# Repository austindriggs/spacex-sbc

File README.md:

# SpaceX SBC PCB Design by Austin Driggs

## INTRODUCTION

This repository contains the complete PCB architecture and design process for a custom Single Board Computer (SBC), prepared for a technical interview presentation for a PCB Design Engineer at SpaceX before I graduated from WVU. It walks through component package selection, power budget calculations, SoC and DDR3 memory constraint analysis, and 8-layer stackup optimization.

> **Disclaimer:** This project is an independent personal design exercise created solely for educational and portfolio demonstration purposes. It is not affiliated with, endorsed by, sponsored by, or associated with Space Exploration Technologies Corp. (SpaceX). All trademarks, logos, and brand names mentioned herein belong to their respective owners.

## PRESENTATION

### Prompt

- You are working with a design engineer on a small computer board.
- The computer board has a SoC, DDR3 DRAM, NAND flash, DC input that is converted to 5V and 3.3V using an onboard DC/DC converter, I/O circuits, etc.
- The SoC is available in BGA, QFN, QFP, bare die. The package outline varies between 8mm x 8mm to 40mm x 40mm depending on the ball/pin pitch which varies between 0.4mm to 1.0mm
- The NAND flash is available in BGA, QFN, and QFP
- The SoC consumes 5W, the DRAM 1W, the NAND flash 0.5W
- You have to help the engineer define the board size, component placement, component selection because the components come in different sizes, footprints, etc, select the board stack up and board technology. 

### Personal Notes

26 pin rpi GPIO: 

The DDR3 DRAM x16 is a single IC, so we won't need Fly-By-Topology (for addr and clk) and the extra layout space that two x8 ICs would take up.
Also assuming DDR3 and not DDR3L since that's what the block diagram is. DDR3 uses standard operating voltage of 1.5V (instead of L of 1.25V).
Also assuming that since its DDR3, it has On-Die-Termination (ODT) for the resistors.

NAND Flash: can be 8 or 16 bit. For 8 bit, you can use the same IC but NC D8-D15. `Note:  Booting on 16-bit NAND Flash is not possible; only 8-bit NAND Flash memories are supported.`

What is RS232? [The RS-232 protocol](https://youtu.be/AHYNxpqKqwo?si=b2U9MRt10fqlJJua) by [Ben Eater](https://www.youtube.com/@BenEater).

Power supplies:
- 3.3V and 5V required
	- uP 5W/3.3V = 1.515A -> 3-5 A supply
- 1.8V for NAND Flash
	- 0.5W = 0.278A -> 0.5A supply 
- 1.5V (really 1.35V) for DDR3(L) and for the uP
	- DRAM 1W = 0.667A -> 2A
- 3.3V is Vdd for the uP
- 1.25V is Vcore for the uP 
- Summary:
- 5V @ 3A
- 3.3V @ 3A

https://www.digikey.com/en/products/detail/texas-instruments/TPS5430DDA/968136

### Questions for the Engineer

Higher Priority:
1. Are there any monetary constraints for the parts or for the manufacturing process?
2. Are there any mechanical or enclosure contraints? Do the IO and power connectors or mounts have to go in a specific location?
3. Are there any environmental constraints: space, thermal relief, EMC/EMI requirements?
4. What type of processing power does the board require? What's the target speed for the SoC and DDR3 DRAM?
5. Is there a specific processor family or architecture required for the project?
6. The voltage input is flexible (8V to 30V), but will the power be constant?
7. Can the board be double sided? At least having smaller/thinner components on the bottom.

Higher Affects:
1. BGA pitch, number of layers, via sizes, trace widths, surface finish, dialectric material.
2. Component spacing, ease of routing, total board size, height limitations.
3. External heatsink for the SoC, enclosure grounding, or shielding.
4. Stackup (layer heights and dialectric material), impedance control, length matching/tuning.
5. Limits package availability, power sequencing complexity, peripheral devices, and the software development stack.
6. If the input current is limited to 1A max, it could result in a 22W difference from 8-30V.
7. BGA SoC need capacitors on the directly under the IC to keep them as close as possible to the power pins.

Lower Priority:
1. How is power being input? Does there need to be any protection?
2. What voltage level are the IO circuits (both Analog and Digital)? How are we interfacing with them?
3. How much current will the IO circuits draw? Both the ICs that the SoC connects to and the devices that will connect to the MX34 and Pi headers.
4. How many GB is needed for the DDR3 DRAM? And what configuration?
5. What size and type of NAND Flash is required (by the engineer or the SoC)?

Lower Affects:
1. Input filters, reverse-polarity protection, fusing, PMICs.
2. Logic level shifters, buffers, communication protocols, or any other ICs required between the SoC and the MX34.
3. DC/DC converter selection, copper weight, thermals, PMIC or protection.
4. Routing density and number of address pins required. One x16 vs two x8's.
5. Routing desnity: SPI (fewer pins) vs (more pins) Parallel NAND and their packages.

### Assumptions I've Made

To move the design process along, I made the following assumptions:
1. I could make reasonable upgrades to component technology as long as there wasn't a drastic price difference.
2. Additional regulators: DDR3 requires a +1V5 voltage source (or +1V35 for DDR3L), so we will at least need to add a +1V5 regulator, as well as any additional voltages for the SoC. I would also assume the NAND flash is +1V8.
3. I will calculate the wattage required for each voltage level and then double it for a factor of safety. I would use buck converters for the main voltage levels (+5V and +3V3) and LDO's when applicable. 
4. For a basic SBC with DDR3 speeds (~800 MHz) and relatively short traces, FR4 will be acceptable.
5. I will try to use standard vendor technologies and materials where applicable: trace widths, through hole vias, stackup heights.

### Initial SoC Pin Calculations

Count the number of pins needed:
- DDR3 DRAM x16 = ~50 signal pins
- NAND Flash = ~15 signal pins (for 8-bit flash)
- Raspberry Pi Header = 17 signal pins
- RTC = 2 signal pins
- RS232 and Serial TTL = ~10 signal pins
- CAN Transciever = ~4 signal pins
- Digital and Analog <= 21 signal pins
- Total signal pin estimate = 119

Total number of pins required:
- Total signal pins / estimated 60% of pins are signals = 198.3 total pins
- Due to the significant number of pins and speed of DDR3, I already am thinking that a BGA package would be the best solution for the SoC.
- BGA's are also the most popular package for SoC, allowing for the widest variety of SoC options.

### Initial Power Calculations

Calculate the current output for each power supply:
- If the SoC consumed all +5V: 5W / +5V = 1A.
- +5V at 3A would be sufficent to power the entire board.
- If the SoC consumed all +3V3: 5W / +3V3 = 1.5A.
- +3V3 at 3A would be sufficent to power the entire board.
- NAND: 0.5W / +1V8 = 0.278A -> 0.5A to 1A supply would be sufficient.
- DDR3: 1W / +1V5 = 0.667A -> 1A to 2A supply would be sufficient.

Summary of calculated values:

| Vin   | Vout | Iout | Pout | Regulator      | Pdiss |
| ----- | ---- | ---- | ---- | -------------- | ----- |
| 8-30V | +5V  | 3A   | 15W  | Buck (90% eff) | 1.67W |
| 8-30V | +3V3 | 3A   | 9.9W | Buck (90% eff) | 1.10W |
| +3V3  | +1V8 | 1A   | 1.8W | LDO            | 1.50W |
| +3V3  | +1V5 | 1A   | 1.5W | LDO            | 1.80W |

Maximum amount of input current would be around 5A for the lowest 8V input.

### SoC Research

Inital package research:
- I rounded to 196 total pins which is a common 14x14 BGA package.
- I looked at some other packages, such as 200+ pin QFP or BGA options.
- I also did try to make sure the SoCs I looked at were able to meet every project requirement.

Package analysis:
- I would not use a bare die because of the manufacturing complexity and cost, environmental risks, and a cost vs benifits analysis.
- Standard (single-row) QFN packages max out at around 100 pins. Multi-row QFN do exist, but are less popular.
- QFP packages that are ~200 pins would fit the 40x40mm size constraint, but usually have a small pitch and take up significantly more space than a BGA package.

### SoC Research (image)

### SoC Package Selection

- Since I don't need that many pins, and I'm not too constained on size, I would rather have the larger-pitched and better performance BGA over the smaller-pitched QFP.  (Assuming double sided for BGA capacitors)
- I decided to go with a BGA 11x11mm SoC that had 0.75mm pitch, resulting in a 14x14 grid with 196 total pins, represented by the Microchip SAMA5D. 
- I'm using it to verify and prove my decisions throughout the rest of this presentation, but if this was purely theoretical, I would use either 0.8mm or 1mm pitch as they are more common and make both engineering and manufacturing easier.

A few benefits include:
- BGA has less parasitic inductance compared to QFP.
- BGA has superior thermal management.
- 196 pin BGA only requires around 2-3 signal layers to fan out.
- The relatively large pitch allows plenty of room for vias and dog-bones.

A few drawbacks include:
- BGA's are harder to rework and would require an X-ray to for inspection and QA.
- By choosing exactly the number of pins that I estimated, it doesn't leave much room for flexibility if the board requirements increased.

### SoC Analysis

Right now, I'm thinking that the overall board size will be between 50x50mm and 100x100mm, and I'll keep that in mind when picking out the remaining components.
- I know that I'll have to supply power, have room for the larger MX34 and RPI headers, and all the IO peripherals.
- The SoC will have the DDR, Flash, and RTC close to it.
- The IO peripherals will go between the SoC and the MX34. 
- The regulators will go further away from critical high-speed components.

Next Steps: Focus on designing each 'section' of components, and then combining them on one board.

### SoC Peripherals

- I would use 0201 caps underneath and as close as possible to every power pin.
- I would use larger decoupling capacitors as needed and as recommended by the manufacturerer and datasheet.
- I would leave enough clearence around the SoC to properly fanout all the signals.
- I would also leave room for mounting holes if an external heat sink was required, especially if the SoC consuming 5W.

### DDR3 DRAM x16

- After selecting the SoC, I would look through its datasheet to see if it has prefered components for its memory.
- BGA packages are also the most popular for DDR memory due to the pin density and speed required.
- In this case, the SAMA5D recommends using a **96 pin BGA that's 8x14mm with 0.8mm pitch**.
- This pin layout and pitch aligns well with the SoC pitch, allowing for dogbone vias and enough room to fanout traces.

> MT41K256M16TW
> 32M x 16-bit x 8 Banks (4-Gbit / 512 MB) DDR3L SDRAM, 1.35V nominal supply voltage, Rev. P, FBGA-96 (8x14mm)
> Package_BGA:Micron_FBGA-96_8x14mm_Layout9x16_P0.8mm

### NAND Flash

- I would follow the same process for the NAND Flash, assuming that I wanted to use parallel NAND.
- The datasheet for the SoC also recommended a 63 pin VFBGA  that's 9x11mm with 0.8mm pitch.
- While TSOP is another popular package, this BGA pin layout and pitch aligns well with the SoC, resulting in about the same requirements for manufacturing (via and trace sizes, room to fanout, etc).

> MT29F2G08ABDHC
> FLASH - NAND Memory IC 2Gbit Parallel 63-VFBGA (10.5x13)
> Package_BGA:BGA-63_9x11mm_Layout10x12_P0.8mm

### Power Input and Regulation

Referencing the table I made earlier, I would search both Digikey/Mouser and the SoC datasheet for appropriate power supplies. For this demo, I decided on the following:
- +5V and +3V3: TI TPS5430DDA adjustable buck switching regulator with 3A continuous output in an 8-PowerSOIC package.
- SOIC are a popular choice for this, and the large ground pad benifits thermals and efficiency.
- SoC/DDR/NAND Voltages: Microchip MCP16501 PMIC that outputs all other required voltages, at 1A each, and in a small QFN-24 4x4mm package with 0.5mm pitch and 2.7x2.7mm EP.
- The input connector is a Molex Microfit+, which is capable of over 10A of input current.

### CAN, RS232, and RTC

- Since this is a generic SBC, I would pick out the rest of the parts based on what's popular, what I've used before and is easy to assemble, and what we commonly use here or already have in stock.
- I would also try to balance the cost of the component, size, and complexity compared to the requirement. 
- I ended up going with the following:
	- CAN: Microchip MCP2562 in a SOIC-8 3.9 x 4.9 mm package with 1.27mm pitch.
	- RS232: TI MAX3221 in a SSOP-16 4.4 x 5.2 mm package with 0.65mm pitch.
	- RTC: SOIC-8 or DFN-8 if an external RTC is required. Some have built in crystals.
	- XTAL: Standard 4-pin SMD 2.5 x 2.0 mm package at 32.768 kHz.

### Digital Output Drivers and Analog Input Conditioning

- I wasn't entirely sure what to do with the digital and analog sections, so I've left plenty of room for placeholder ICs. I would need more information from the engineer.
- For verifying the 196-pin SoC, I created 8 spare signals for the digital output driver and 13 for the analog input conditioning.
- Possibilities include: logic level shifters, buffers, communication protocols, or any other ICs required between the SoC and the MX34.
- The biggest contributing factor is how much current that these signals would be driving, and if that current had to be supplied from one of the onboard regulators to an MX34 power pin.
- The MX34 is rated for 3A per pin, but hopefully we won't reach that.

### Stackup Layer Selection: 6-Layer

- Based off of the SoC and other selected components, I wanted to try a 6-layer stackup.
- The main contributing factor is the SoC BGA fanout and the DDR3 impedance.
- I would use a prefered vendor and select their standard 6-layer stackup and board height.

1. Signal: Main fanout for the SoC and other BGA components. Optional routing of power.
2. GND: Standard un-split ground plane.
3. Signal: Stripline layer for the DDR3 and other higher-speed signals.
4. Power: Split power planes for all voltage levels, especially for the SoC.
5. GND: Standard un-split ground plane.
6. Signal: Main fanout for the SoC and other BGA components. Optional routing of power.

> https://www.sunstone.com/docs/default-source/layer-stack-up-2022/l06-062-1-hv2.pdf

%% Standard trace width rules use 10 mils per amp for outer layers and 20 mils per amp for inner layers, assuming 1 oz copper. %%

### Stackup Layer Calculations: 6-layer

However, I started calculating and the trace widths needed to be larger than what was possible, especially on the outer layers.

### Stackup Alternatives

Even making the board thinner (1.0mm) and going up to 8 layers did not help routing DDR3 on the outer layers.

### Stackup Layer Selection: 8-Layer

1. Signal: Mixed signal
2. GND
3. Signal: High-speed DDR3
4. Power: Mainly SoC
5. GND
6. Signal: High-speed DDR3
7. GND
8. Signal: Mixed signal

### Stackup Layer Analysis: 8-Layer

Moving to an 8-layer board has many benefits:
- The dual stripline routing helps eliminate EMI and external noise.
- Reduced cross-talk as there's more space for signals to be routed.
- Easier length matching since there's more room.
- Better thermal performance across the board.
- Reduced thermal warpage and better layer symmetry.

Drawbacks:
- Costs more.

### Stackup Layer Calculations: 8-Layer for Sunstone Circuits

### Stackup Layer Calculations: 8-Layer for JLCPCB

### Block Diagram Layout

### Optimizing Component Placement

- I assigned net labels to the different signals and color-coded them.

At this point, I would verify this layout and 3D model with any mechanical engineers.

### Routing Power

### Routing Signals

- I moved pins around inside of the schematic (assuming that all GPIO were able to have most functionalities).

### Cost Analysis

Inputs:
- Quantity: 10
- Advanced PCB/PCBA
- 8 layers, 75x75mm
- 1.6mm thickness
- HASL Finish, FR4 TG170
- 1oz copper layers
- Impedance controlled
- Min hole size = 0.2mm
- Stackup: JLC081611-3313

Total = $259.34 for 10 boards = $25.93 per board.

## CONCLUSION

- You are working with a design engineer on a small computer board.
- The computer board has a SoC, DDR3 DRAM, NAND flash, DC input that is converted to 5V and 3.3V using an onboard DC/DC converter, I/O circuits, etc.
- The SoC is available in BGA, QFN, QFP, bare die. The package outline varies between 8mm x 8mm to 40mm x 40mm depending on the ball/pin pitch which varies between 0.4mm to 1.0mm
- The NAND flash is available in BGA, QFN, and QFP
- The SoC consumes 5W, the DRAM 1W, the NAND flash 0.5W
- You have to help the engineer define the board size, component placement, component selection because the components come in different sizes, footprints, etc, select the board stack up and board technology. 

- Started with asking questions, defining requirements, and establising assumptions.
- Calculations for power, number of SoC pins, and trace impedance values.
- Researched, analyzed, and selected a SoC package.
- Selected SoC peripherals including the DRAM, Flash, and RTC.
- Determined types and ratings for the voltage regulators.
- Designed the stackup, technology, and component placement.

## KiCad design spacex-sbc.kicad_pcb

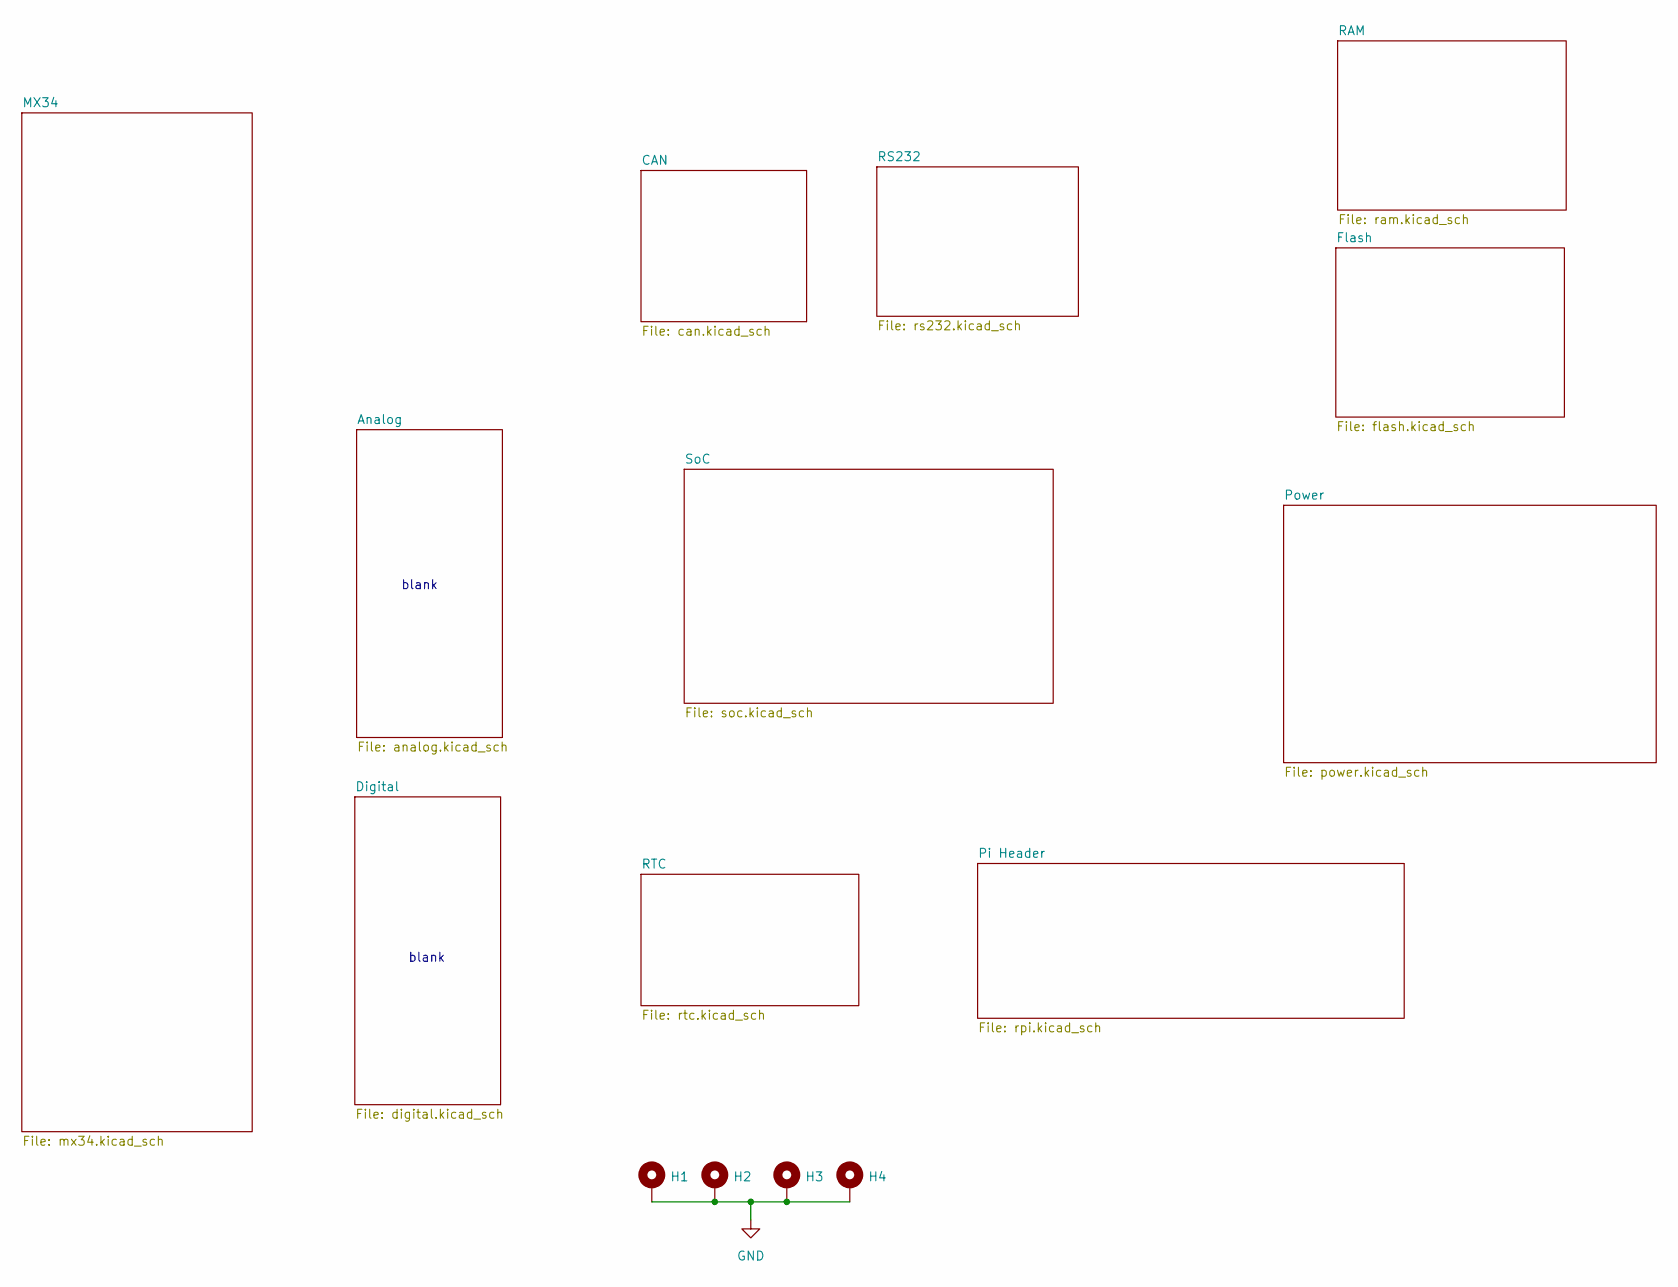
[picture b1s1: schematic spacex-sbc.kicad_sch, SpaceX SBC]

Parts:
H1, H2, H3, H4: MountingHole_Pad; MountingHole_3.2mm_M3_Pad

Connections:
GND: H1.1, H2.1, H3.1, H4.1; also elsewhere on the board

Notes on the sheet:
blank

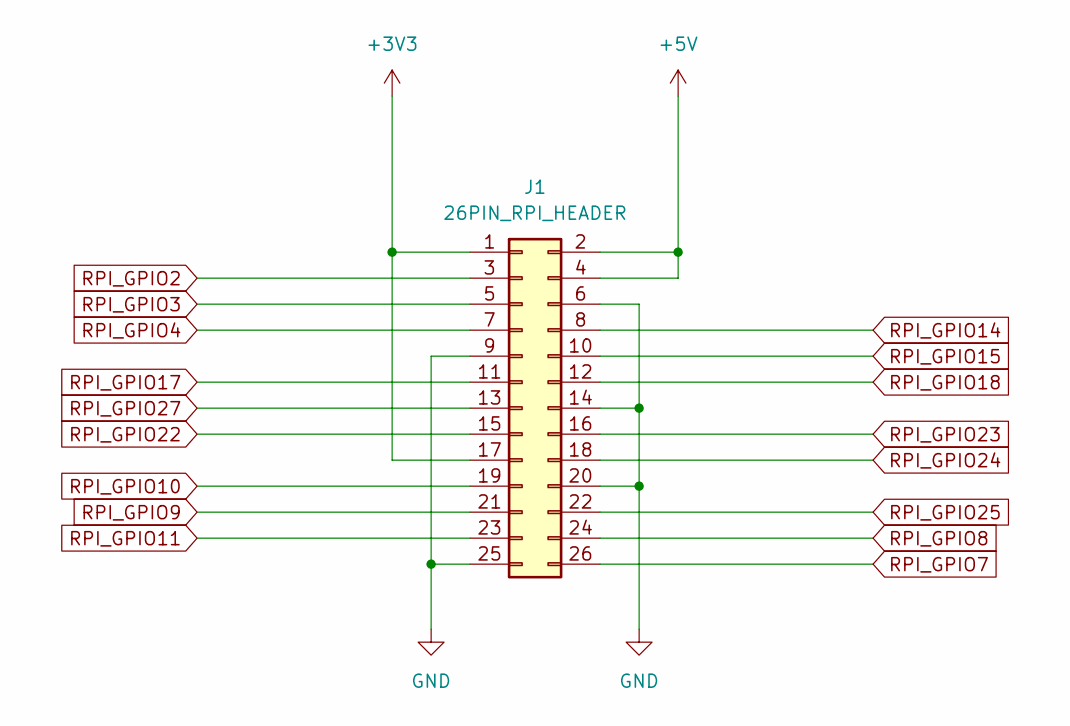
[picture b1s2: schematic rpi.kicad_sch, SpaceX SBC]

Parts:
J1: 26PIN_RPI_HEADER; PinSocket_2x13_P2.54mm_Vertical

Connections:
+3V3: J1.1, J1.17; also elsewhere on the board
+5V: J1.2, J1.4; also elsewhere on the board
GND: J1.6, J1.9, J1.14, J1.20, J1.25; also elsewhere on the board
RPI_GPIO2: J1.3; also elsewhere on the board
RPI_GPIO3: J1.5; also elsewhere on the board
RPI_GPIO4: J1.7; also elsewhere on the board
RPI_GPIO7: J1.26; also elsewhere on the board
RPI_GPIO8: J1.24; also elsewhere on the board
RPI_GPIO9: J1.21; also elsewhere on the board
RPI_GPIO10: J1.19; also elsewhere on the board
RPI_GPIO11: J1.23; also elsewhere on the board
RPI_GPIO14: J1.8; also elsewhere on the board
RPI_GPIO15: J1.10; also elsewhere on the board
RPI_GPIO17: J1.11; also elsewhere on the board
RPI_GPIO18: J1.12; also elsewhere on the board
RPI_GPIO22: J1.15; also elsewhere on the board
RPI_GPIO23: J1.16; also elsewhere on the board
RPI_GPIO24: J1.18; also elsewhere on the board
RPI_GPIO25: J1.22; also elsewhere on the board
RPI_GPIO27: J1.13; also elsewhere on the board

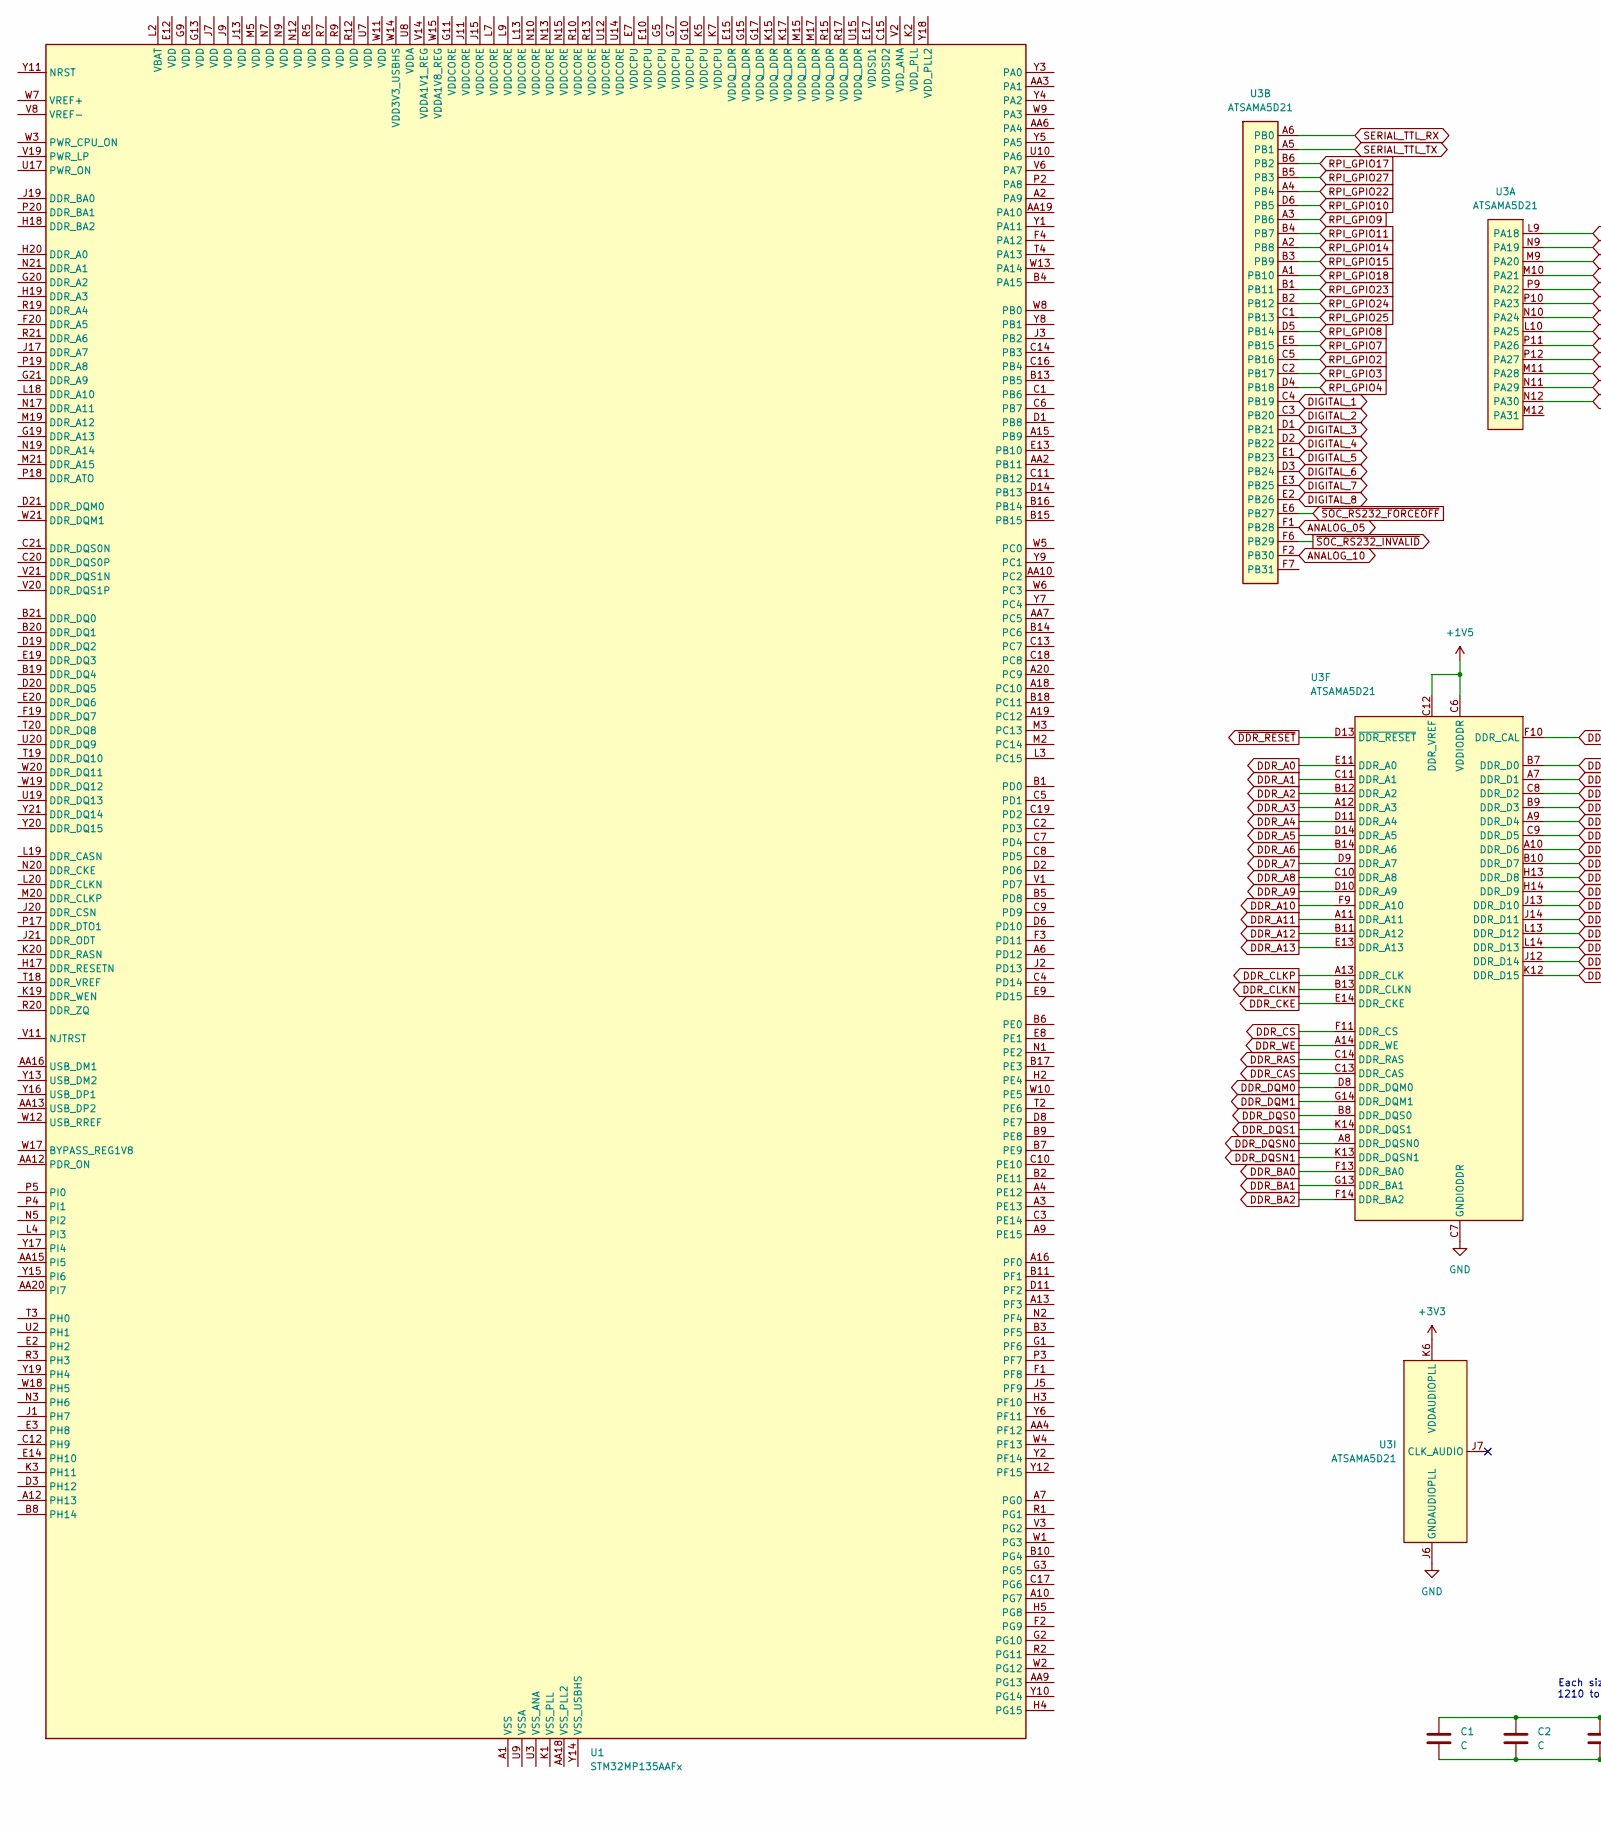
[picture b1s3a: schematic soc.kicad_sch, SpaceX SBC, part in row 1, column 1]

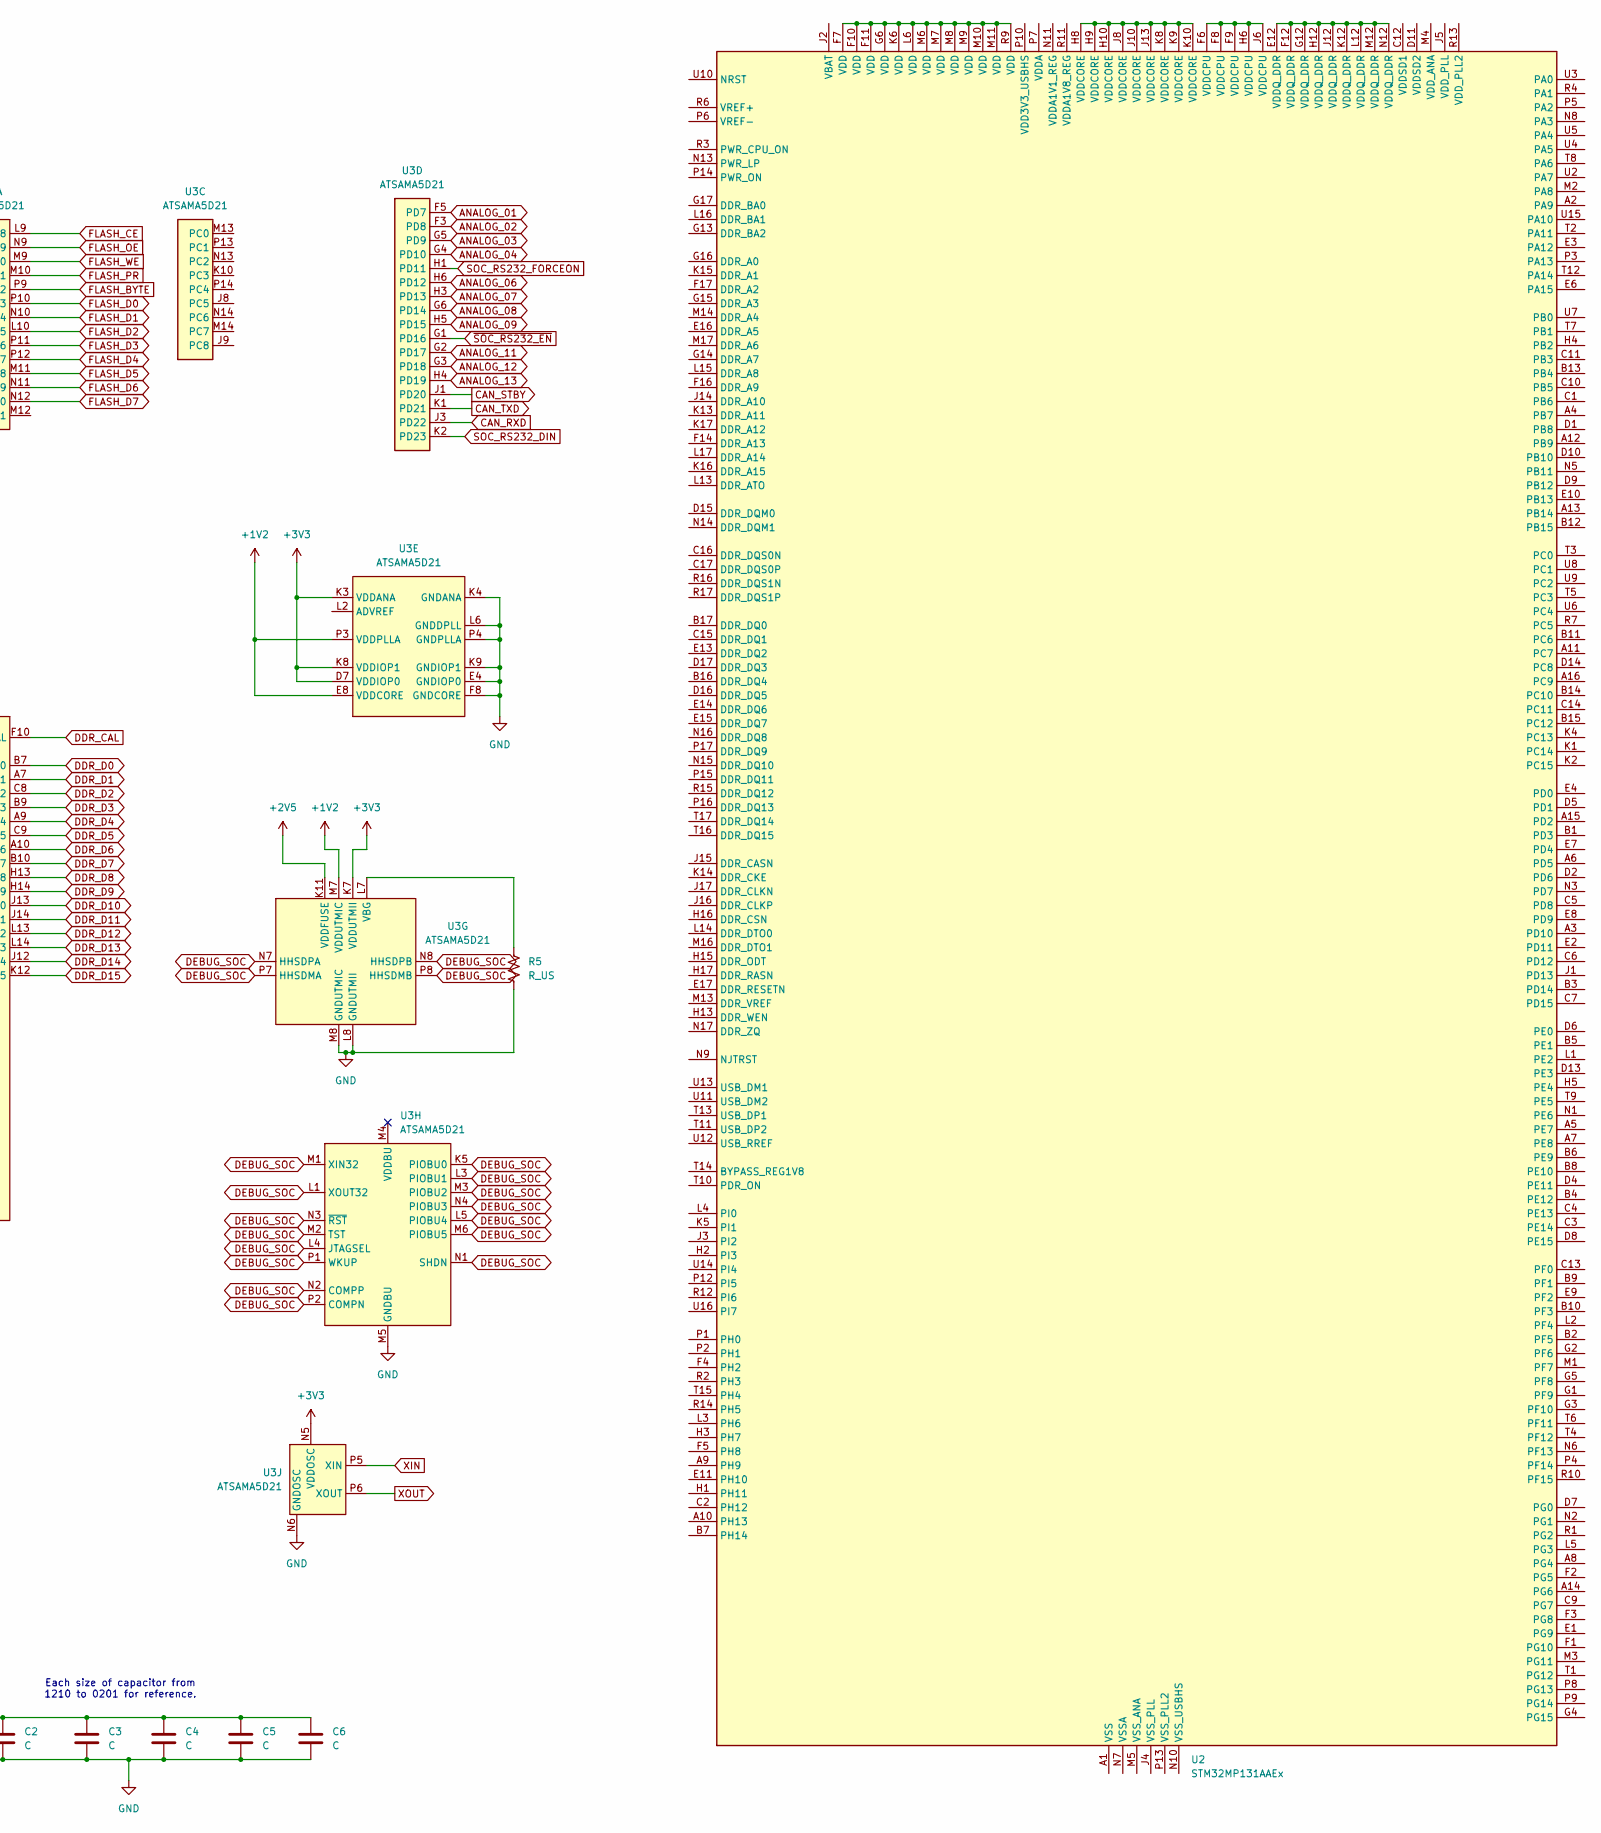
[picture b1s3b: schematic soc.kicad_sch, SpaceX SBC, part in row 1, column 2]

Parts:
C1: C; C_1210_3225Metric
C2: C; C_1206_3216Metric
C3: C; C_0805_2012Metric
C4: C; C_0603_1608Metric
C5: C; C_0402_1005Metric
C6: C; C_0201_0603Metric
R5: R_US; R_0402_1005Metric
U1: STM32MP135AAFx; ST_TFBGA-320_11x11mm_Layout21x21_P0.5mm
U2: STM32MP131AAEx; LFBGA-289_14x14mm_Layout17x17_P0.8mm
U3: ATSAMA5D21; Microchip_TFBGA-196_11x11mm_Layout14x14_P0.75mm_SMD

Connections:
+1V2: U3.E8 (VDDCORE), U3.G8 (VDDCORE), U3.H8 (VDDCORE), U3.H9 (VDDCORE), U3.J5 (VDDCORE), U3.M7 (VDDUTMIC), U3.P3 (VDDPLLA)
+1V5: U3.C6 (VDDIODDR), U3.C12 (DDR_VREF), U3.E10 (VDDIODDR), U3.E12 (VDDIODDR), U3.G10 (VDDIODDR), U3.G12 (VDDIODDR), U3.H11 (VDDIODDR), U3.H12 (DDR_VREF), U3.J10 (VDDIODDR); also elsewhere on the board
+2V5: U3.K11 (VDDFUSE)
+3V3: U3.D7 (VDDIOP0), U3.F4 (VDDIOP0), U3.H2 (VDDANA), U3.K3 (VDDANA), U3.K6 (VDDAUDIOPLL), U3.K7 (VDDUTMII), U3.K8 (VDDIOP1), U3.L11 (VDDIOP1), U3.N5 (VDDOSC); also elsewhere on the board
ANALOG_01: U3.F5 (PD7); also elsewhere on the board
ANALOG_02: U3.F3 (PD8); also elsewhere on the board
ANALOG_03: U3.G5 (PD9); also elsewhere on the board
ANALOG_04: U3.G4 (PD10); also elsewhere on the board
ANALOG_05: U3.F1 (PB28); also elsewhere on the board
ANALOG_06: U3.H6 (PD12); also elsewhere on the board
ANALOG_07: U3.H3 (PD13); also elsewhere on the board
ANALOG_08: U3.G6 (PD14); also elsewhere on the board
ANALOG_09: U3.H5 (PD15); also elsewhere on the board
ANALOG_10: U3.F2 (PB30); also elsewhere on the board
ANALOG_11: U3.G2 (PD17); also elsewhere on the board
ANALOG_12: U3.G3 (PD18); also elsewhere on the board
ANALOG_13: U3.H4 (PD19); also elsewhere on the board
CAN_RXD: U3.J3 (PD22); also elsewhere on the board
CAN_STBY: U3.J1 (PD20); also elsewhere on the board
CAN_TXD: U3.K1 (PD21); also elsewhere on the board
DDR_A0: U3.E11 (DDR_A0); also elsewhere on the board
DDR_A1: U3.C11 (DDR_A1); also elsewhere on the board
DDR_A2: U3.B12 (DDR_A2); also elsewhere on the board
DDR_A3: U3.A12 (DDR_A3); also elsewhere on the board
DDR_A4: U3.D11 (DDR_A4); also elsewhere on the board
DDR_A5: U3.D14 (DDR_A5); also elsewhere on the board
DDR_A6: U3.B14 (DDR_A6); also elsewhere on the board
DDR_A7: U3.D9 (DDR_A7); also elsewhere on the board
DDR_A8: U3.C10 (DDR_A8); also elsewhere on the board
DDR_A9: U3.D10 (DDR_A9); also elsewhere on the board
DDR_A10: U3.F9 (DDR_A10); also elsewhere on the board
DDR_A11: U3.A11 (DDR_A11); also elsewhere on the board
DDR_A12: U3.B11 (DDR_A12); also elsewhere on the board
DDR_A13: U3.E13 (DDR_A13); also elsewhere on the board
DDR_BA0: U3.F13 (DDR_BA0); also elsewhere on the board
DDR_BA1: U3.G13 (DDR_BA1); also elsewhere on the board
DDR_BA2: U3.F14 (DDR_BA2); also elsewhere on the board
DDR_CAL: U3.F10 (DDR_CAL)
DDR_CAS: U3.C13 (DDR_CAS); also elsewhere on the board
DDR_CKE: U3.E14 (DDR_CKE); also elsewhere on the board
DDR_CLKN: U3.B13 (DDR_CLKN); also elsewhere on the board
DDR_CLKP: U3.A13 (DDR_CLK); also elsewhere on the board
DDR_CS: U3.F11 (DDR_CS); also elsewhere on the board
DDR_D0: U3.B7 (DDR_D0); also elsewhere on the board
DDR_D1: U3.A7 (DDR_D1); also elsewhere on the board
DDR_D2: U3.C8 (DDR_D2); also elsewhere on the board
DDR_D3: U3.B9 (DDR_D3); also elsewhere on the board
DDR_D4: U3.A9 (DDR_D4); also elsewhere on the board
DDR_D5: U3.C9 (DDR_D5); also elsewhere on the board
DDR_D6: U3.A10 (DDR_D6); also elsewhere on the board
DDR_D7: U3.B10 (DDR_D7); also elsewhere on the board
DDR_D8: U3.H13 (DDR_D8); also elsewhere on the board
DDR_D9: U3.H14 (DDR_D9); also elsewhere on the board
DDR_D10: U3.J13 (DDR_D10); also elsewhere on the board
DDR_D11: U3.J14 (DDR_D11); also elsewhere on the board
DDR_D12: U3.L13 (DDR_D12); also elsewhere on the board
DDR_D13: U3.L14 (DDR_D13); also elsewhere on the board
DDR_D14: U3.J12 (DDR_D14); also elsewhere on the board
DDR_D15: U3.K12 (DDR_D15); also elsewhere on the board
DDR_DQM0: U3.D8 (DDR_DQM0); also elsewhere on the board
DDR_DQM1: U3.G14 (DDR_DQM1); also elsewhere on the board
DDR_DQS0: U3.B8 (DDR_DQS0); also elsewhere on the board
DDR_DQS1: U3.K14 (DDR_DQS1); also elsewhere on the board
DDR_DQSN0: U3.A8 (DDR_DQSN0); also elsewhere on the board
DDR_DQSN1: U3.K13 (DDR_DQSN1); also elsewhere on the board
DDR_RAS: U3.C14 (DDR_RAS); also elsewhere on the board
DDR_WE: U3.A14 (DDR_WE); also elsewhere on the board
DEBUG_SOC: U3.K5 (PIOBU0), U3.L1 (XOUT32), U3.L3 (PIOBU1), U3.L4 (JTAGSEL), U3.L5 (PIOBU4), U3.M1 (XIN32), U3.M2 (TST), U3.M3 (PIOBU2), U3.M6 (PIOBU5), U3.N1 (SHDN), U3.N2 (COMPP), U3.N3 (~RST), U3.N4 (PIOBU3), U3.N7 (HHSDPA), U3.N8 (HHSDPB), U3.P1 (WKUP), U3.P2 (COMPN), U3.P7 (HHSDMA), U3.P8 (HHSDMB)
DIGITAL_1: U3.C4 (PB19); also elsewhere on the board
DIGITAL_2: U3.C3 (PB20); also elsewhere on the board
DIGITAL_3: U3.D1 (PB21); also elsewhere on the board
DIGITAL_4: U3.D2 (PB22); also elsewhere on the board
DIGITAL_5: U3.E1 (PB23); also elsewhere on the board
DIGITAL_6: U3.D3 (PB24); also elsewhere on the board
DIGITAL_7: U3.E3 (PB25); also elsewhere on the board
DIGITAL_8: U3.E2 (PB26); also elsewhere on the board
FLASH_BYTE: U3.L9 (PA18), U3.P9 (PA22); also elsewhere on the board
FLASH_D0: U3.P10 (PA23)
FLASH_D1: U3.N10 (PA24); also elsewhere on the board
FLASH_D2: U3.L10 (PA25); also elsewhere on the board
FLASH_D3: U3.P11 (PA26); also elsewhere on the board
FLASH_D4: U3.P12 (PA27)
FLASH_D5: U3.M11 (PA28); also elsewhere on the board
FLASH_D6: U3.N11 (PA29); also elsewhere on the board
FLASH_D7: U3.N12 (PA30); also elsewhere on the board
FLASH_OE: U3.N9 (PA19); also elsewhere on the board
FLASH_PR: U3.M10 (PA21); also elsewhere on the board
FLASH_WE: U3.M9 (PA20); also elsewhere on the board
GND: C1.2, C2.2, C3.2, C4.2, C5.2, C6.2, R5.2, U3.C7 (GNDIODDR), U3.D12 (GNDIODDR), U3.E4 (GNDIOP0), U3.E7 (GNDIOP0), U3.E9 (GNDIODDR), U3.F8 (GNDCORE), U3.F12 (GNDIODDR), U3.G7 (GNDCORE), U3.G9 (GNDCORE), U3.G11 (GNDIODDR), U3.H7 (GNDCORE), U3.H10 (GNDIODDR), U3.J2 (GNDANA), U3.J4 (GNDCORE), U3.J6 (GNDAUDIOPLL), U3.J11 (GNDIODDR), U3.K4 (GNDANA), U3.K9 (GNDIOP1), U3.L6 (GNDDPLL), U3.L8 (GNDUTMII), U3.L12 (GNDIOP1), U3.M5 (GNDBU), U3.M8 (GNDUTMIC), U3.N6 (GNDOSC), U3.P4 (GNDPLLA); also elsewhere on the board
unnamed: C1.1, C2.1, C3.1, C4.1, C5.1, C6.1
unnamed: U1.A1 (VSS), U1.A21 (VSS), U1.AA1 (VSS), U1.AA21 (VSS), U1.B12 (VSS), U1.D16 (VSS), U1.E5 (VSS), U1.E6 (VSS), U1.E11 (VSS), U1.E16 (VSS), U1.F5 (VSS), U1.F17 (VSS), U1.F18 (VSS), U1.F21 (VSS), U1.G8 (VSS), U1.G12 (VSS), U1.G14 (VSS), U1.H7 (VSS), U1.H15 (VSS), U1.J10 (VSS), U1.J12 (VSS), U1.K9 (VSS), U1.K10 (VSS), U1.K11 (VSS), U1.K12 (VSS), U1.K13 (VSS), U1.K21 (VSS), U1.L5 (VSS), U1.L10 (VSS), U1.L12 (VSS), U1.L15 (VSS), U1.L17 (VSS), U1.M1 (VSS), U1.M7 (VSS), U1.M9 (VSS), U1.M10 (VSS), U1.M11 (VSS), U1.M12 (VSS), U1.M13 (VSS), U1.N11 (VSS), U1.P7 (VSS), U1.P15 (VSS), U1.R8 (VSS), U1.R11 (VSS), U1.R14 (VSS), U1.T1 (VSS), U1.T5 (VSS), U1.T17 (VSS), U1.T21 (VSS), U1.U5 (VSS), U1.U6 (VSS), U1.U11 (VSS), U1.U13 (VSS), U1.U16 (VSS), U1.V16 (VSS), U1.W16 (VSS)
unnamed: U2.F7 (VDD), U2.F10 (VDD), U2.F11 (VDD), U2.G6 (VDD), U2.K6 (VDD), U2.L6 (VDD), U2.M6 (VDD), U2.M7 (VDD), U2.M8 (VDD), U2.M9 (VDD), U2.M10 (VDD), U2.M11 (VDD), U2.R9 (VDD)
unnamed: U2.H8 (VDDCORE), U2.H9 (VDDCORE), U2.H10 (VDDCORE), U2.J8 (VDDCORE), U2.J10 (VDDCORE), U2.J13 (VDDCORE), U2.K8 (VDDCORE), U2.K9 (VDDCORE), U2.K10 (VDDCORE)
unnamed: U2.F6 (VDDCPU), U2.F8 (VDDCPU), U2.F9 (VDDCPU), U2.H6 (VDDCPU), U2.J6 (VDDCPU)
unnamed: U2.E12 (VDDQ_DDR), U2.F12 (VDDQ_DDR), U2.G12 (VDDQ_DDR), U2.H12 (VDDQ_DDR), U2.J12 (VDDQ_DDR), U2.K12 (VDDQ_DDR), U2.L12 (VDDQ_DDR), U2.M12 (VDDQ_DDR), U2.N12 (VDDQ_DDR)
unnamed: U2.A1 (VSS), U2.A17 (VSS), U2.C8 (VSS), U2.D3 (VSS), U2.D12 (VSS), U2.E5 (VSS), U2.F13 (VSS), U2.F15 (VSS), U2.G7 (VSS), U2.G8 (VSS), U2.G9 (VSS), U2.G10 (VSS), U2.G11 (VSS), U2.H7 (VSS), U2.H11 (VSS), U2.H14 (VSS), U2.J7 (VSS), U2.J9 (VSS), U2.J11 (VSS), U2.K3 (VSS), U2.K7 (VSS), U2.K11 (VSS), U2.L7 (VSS), U2.L8 (VSS), U2.L9 (VSS), U2.L10 (VSS), U2.L11 (VSS), U2.M15 (VSS), U2.N4 (VSS), U2.P11 (VSS), U2.R5 (VSS), U2.R8 (VSS), U2.U1 (VSS), U2.U17 (VSS)
unnamed: R5.1, U3.L7 (VBG)
RPI_GPIO2: U3.C5 (PB16); also elsewhere on the board
RPI_GPIO3: U3.C2 (PB17); also elsewhere on the board
RPI_GPIO4: U3.D4 (PB18); also elsewhere on the board
RPI_GPIO7: U3.E5 (PB15); also elsewhere on the board
RPI_GPIO8: U3.D5 (PB14); also elsewhere on the board
RPI_GPIO9: U3.A3 (PB6); also elsewhere on the board
RPI_GPIO10: U3.D6 (PB5); also elsewhere on the board
RPI_GPIO11: U3.B4 (PB7); also elsewhere on the board
RPI_GPIO14: U3.A2 (PB8); also elsewhere on the board
RPI_GPIO15: U3.B3 (PB9); also elsewhere on the board
RPI_GPIO17: U3.B6 (PB2); also elsewhere on the board
RPI_GPIO18: U3.A1 (PB10); also elsewhere on the board
RPI_GPIO22: U3.A4 (PB4); also elsewhere on the board
RPI_GPIO23: U3.B1 (PB11); also elsewhere on the board
RPI_GPIO24: U3.B2 (PB12); also elsewhere on the board
RPI_GPIO25: U3.C1 (PB13); also elsewhere on the board
RPI_GPIO27: U3.B5 (PB3); also elsewhere on the board
SERIAL_TTL_RX: U3.A6 (PB0); also elsewhere on the board
SERIAL_TTL_TX: U3.A5 (PB1); also elsewhere on the board
SOC_RS232_DIN: U3.K2 (PD23); also elsewhere on the board
SOC_RS232_FORCEON: U3.H1 (PD11); also elsewhere on the board
XIN: U3.P5 (XIN); also elsewhere on the board
XOUT: U3.P6 (XOUT); also elsewhere on the board
~DDR_RESET: U3.D13 (~DDR_RESET); also elsewhere on the board
~SOC_RS232_EN: U3.G1 (PD16); also elsewhere on the board
~SOC_RS232_FORCEOFF: U3.E6 (PB27); also elsewhere on the board
~SOC_RS232_INVALID: U3.F6 (PB29); also elsewhere on the board

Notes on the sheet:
Each size of capacitor from 1210 to 0201 for reference.

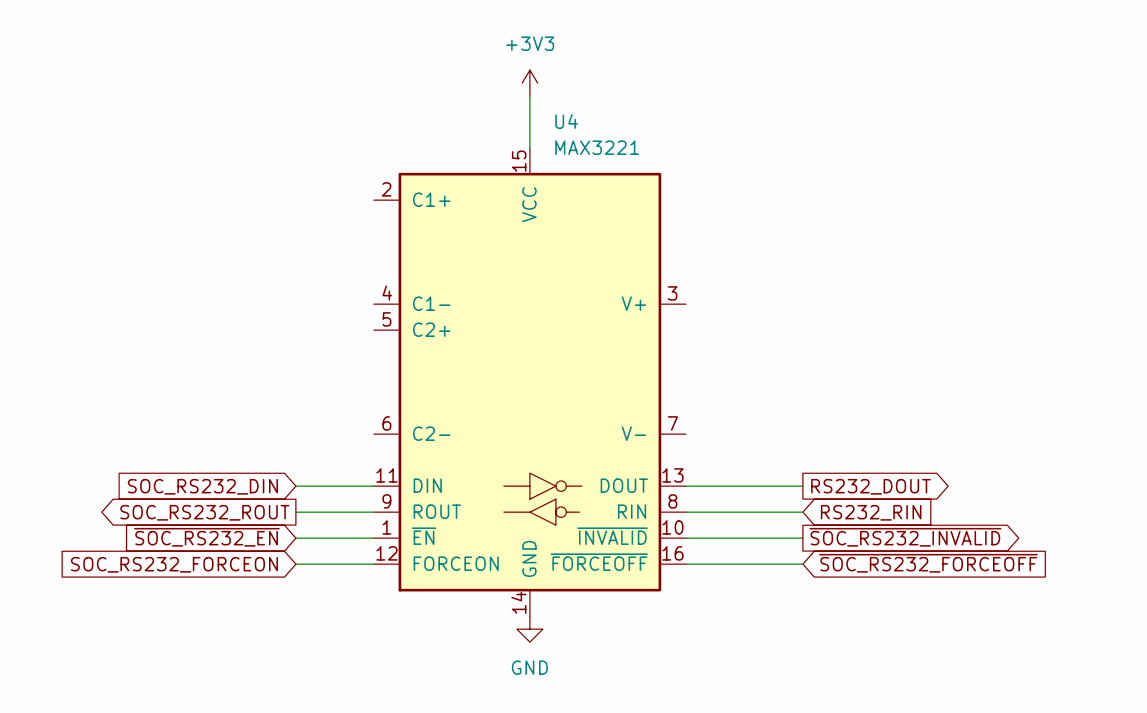
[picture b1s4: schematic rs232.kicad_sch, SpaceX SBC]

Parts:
U4: MAX3221; SSOP-16_4.4x5.2mm_P0.65mm

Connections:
+3V3: U4.15 (VCC); also elsewhere on the board
GND: U4.14 (GND); also elsewhere on the board
RS232_DOUT: U4.13 (DOUT); also elsewhere on the board
RS232_RIN: U4.8 (RIN); also elsewhere on the board
SOC_RS232_DIN: U4.11 (DIN); also elsewhere on the board
SOC_RS232_FORCEON: U4.12 (FORCEON); also elsewhere on the board
SOC_RS232_ROUT: U4.9 (ROUT)
~SOC_RS232_EN: U4.1 (~EN); also elsewhere on the board
~SOC_RS232_FORCEOFF: U4.16 (~FORCEOFF); also elsewhere on the board
~SOC_RS232_INVALID: U4.10 (~INVALID); also elsewhere on the board

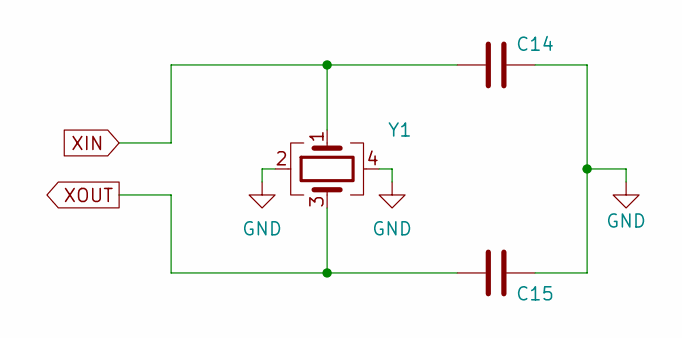
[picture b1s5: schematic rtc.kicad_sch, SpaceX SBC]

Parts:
C14, C15: 12pF; C_0402_1005Metric; Manufacturer Part Number C0603C120K5RACTU
Y1: 8MHz; Crystal_SMD_1210-4Pin_1.2x1.0mm; Manufacturer Part Number FL0800011Q

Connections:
GND: C14.1, C15.1, Y1.2, Y1.4; also elsewhere on the board
XIN: C14.2, Y1.1; also elsewhere on the board
XOUT: C15.2, Y1.3; also elsewhere on the board
